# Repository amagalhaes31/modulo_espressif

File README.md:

# Modulo Conectividade com Espressif
Módulo Espressif com conectividades Wi-Fi, ETH, LTE, GPS e BLE.

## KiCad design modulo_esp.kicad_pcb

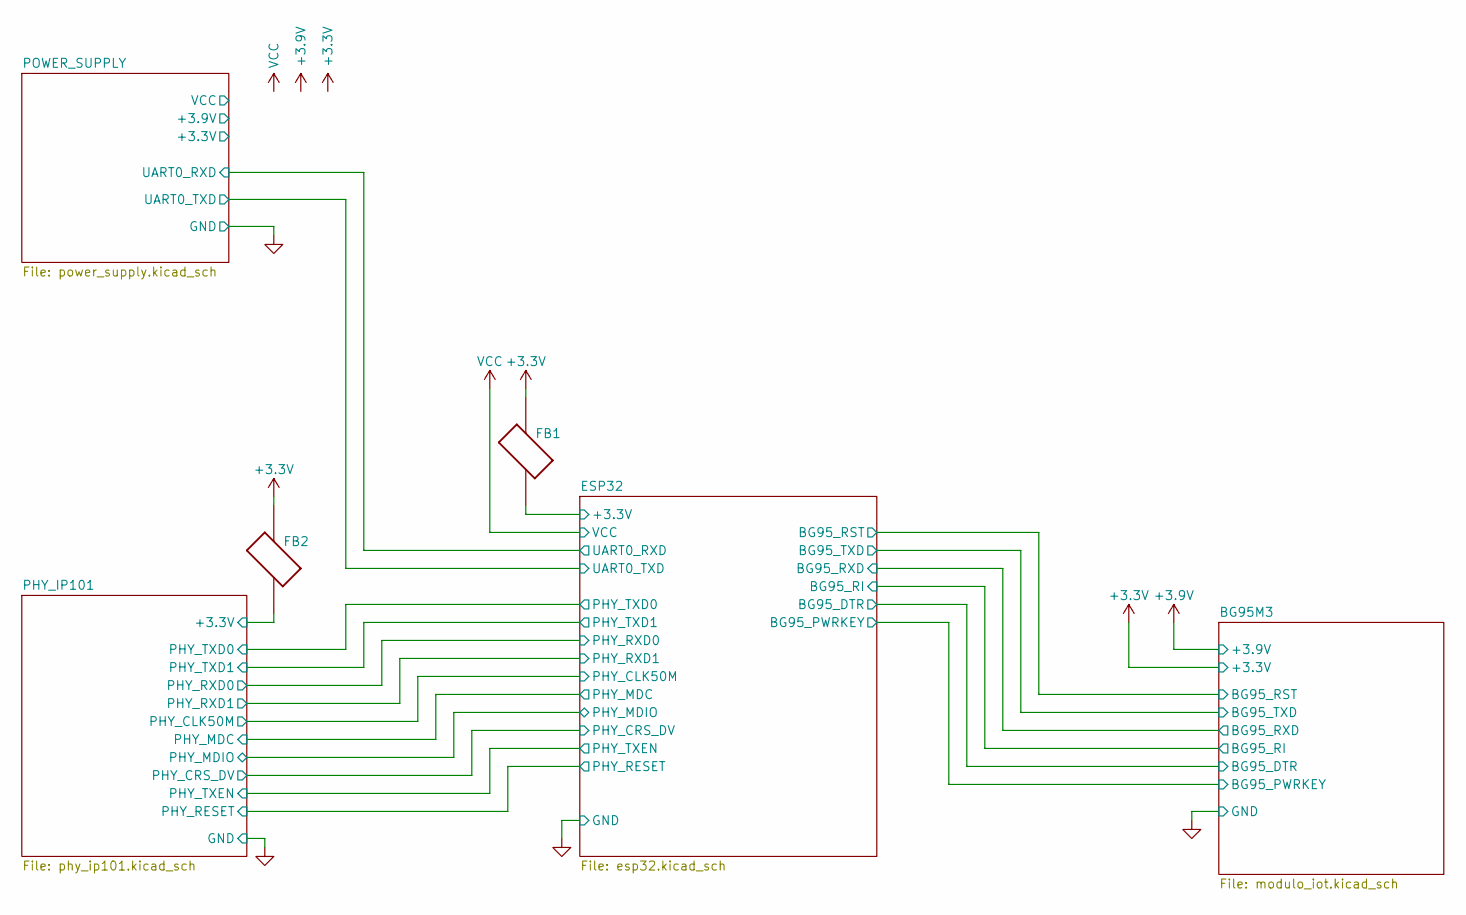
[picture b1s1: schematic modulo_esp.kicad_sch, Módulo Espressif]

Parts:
FB1, FB2: MPZ2012S102AT000; BEADC2012X105N; PARTREV 20190423

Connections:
+3V3: FB1.1, FB1.2, FB2.1, FB2.2; also elsewhere on the board

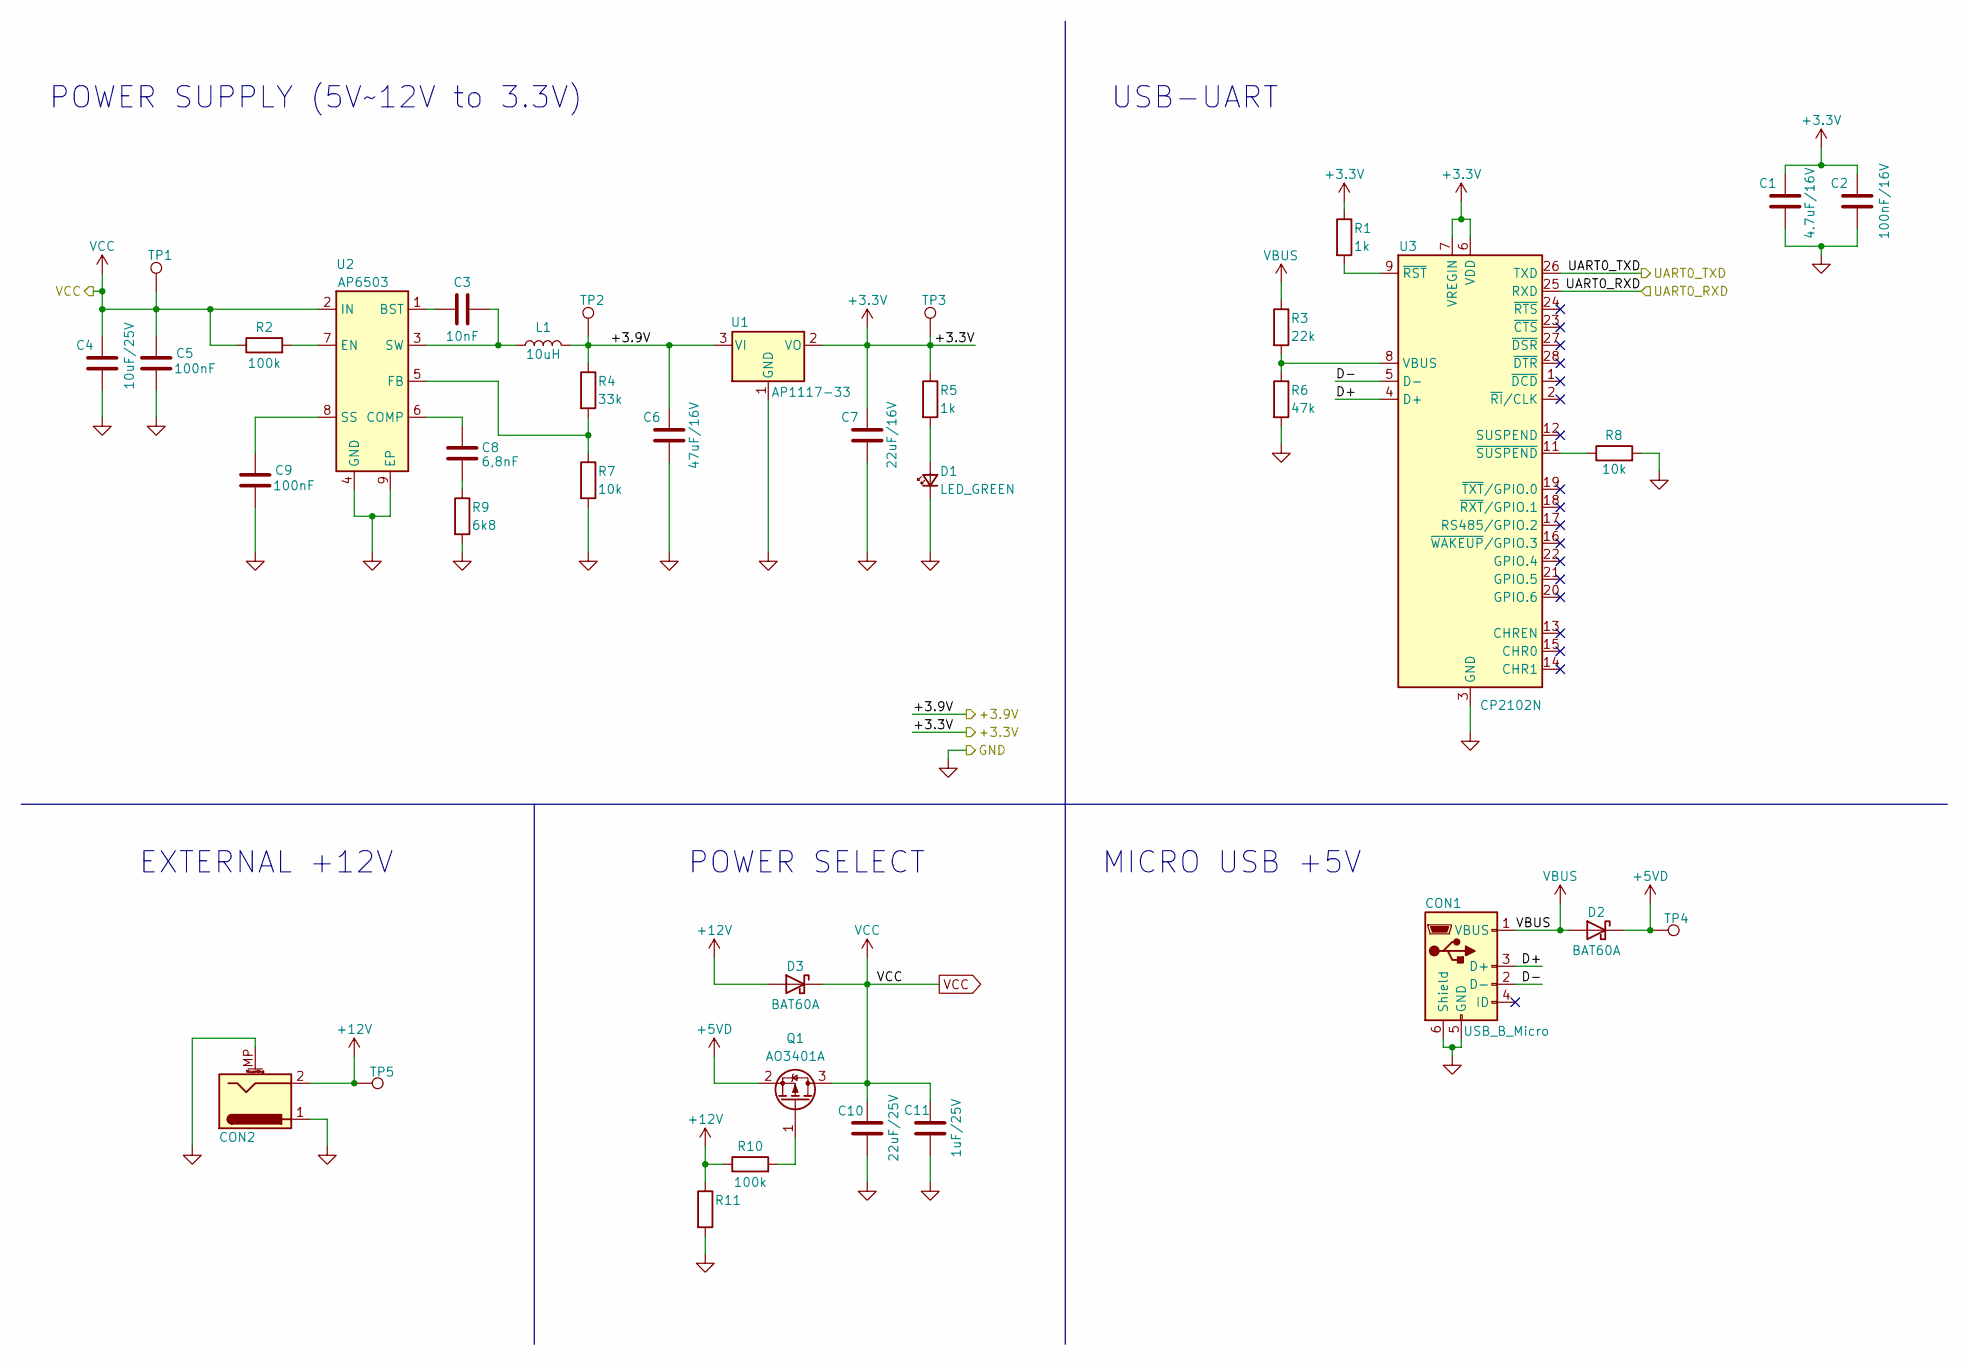
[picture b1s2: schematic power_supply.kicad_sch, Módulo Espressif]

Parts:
C1: 4.7uF/16V; C_1206_3216Metric_Pad1.33x1.80mm_HandSolder
C2: 100nF/16V; C_0603_1608Metric_Pad1.08x0.95mm_HandSolder
C3: 10nF; C_0603_1608Metric_Pad1.08x0.95mm_HandSolder
C4: 10uF/25V; C_1206_3216Metric_Pad1.33x1.80mm_HandSolder
C5, C9: 100nF; C_0603_1608Metric_Pad1.08x0.95mm_HandSolder
C6: 47uF/16V; C_1206_3216Metric_Pad1.33x1.80mm_HandSolder
C7: 22uF/16V; C_1206_3216Metric_Pad1.33x1.80mm_HandSolder
C8: 6,8nF; C_0603_1608Metric_Pad1.08x0.95mm_HandSolder
C10: 22uF/25V; C_1206_3216Metric_Pad1.33x1.80mm_HandSolder
C11: 1uF/25V; C_0603_1608Metric_Pad1.08x0.95mm_HandSolder
CON1: USB_B_Micro; USB_Micro-B_GCT_USB3076-30-A
CON2: Barrel_Jack_MountingPin; BarrelJack_GCT_DCJ200-10-A_Horizontal
D1: LED_GREEN; LED_0603_1608Metric_Pad1.05x0.95mm_HandSolder
D2, D3: BAT60A; D_SOD-323
L1: 10uH; L_Bourns-SRN8040_8x8.15mm
Q1: AO3401A; SOT-23
R1, R5: 1k; R_0603_1608Metric_Pad0.98x0.95mm_HandSolder
R2, R10: 100k; R_0603_1608Metric_Pad0.98x0.95mm_HandSolder
R3: 22k; R_0603_1608Metric_Pad0.98x0.95mm_HandSolder
R4: 33k; R_0603_1608Metric_Pad0.98x0.95mm_HandSolder
R6: 47k; R_0603_1608Metric_Pad0.98x0.95mm_HandSolder
R7, R8: 10k; R_0603_1608Metric_Pad0.98x0.95mm_HandSolder
R9: 6k8; R_0603_1608Metric_Pad0.98x0.95mm_HandSolder
R11: (no value)
TP1, TP2, TP3, TP4, TP5: TestPoint; TestPoint_Pad_1.5x1.5mm
U1: AP1117-33; SOT-223-3_TabPin2
U2: AP6503; SOIC-8-1EP_3.9x4.9mm_P1.27mm_EP2.41x3.81mm_ThermalVias
U3: CP2102N; QFN-28-1EP_5x5mm_P0.5mm_EP3.35x3.35mm

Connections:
+3V3: C1.1, C2.2, C7.1, R1.1, R5.1, TP3.1, U1.2 (VO), U3.6 (VDD), U3.7 (VREGIN); also elsewhere on the board
+5VD: D2.1 (K), Q1.2 (S), TP4.1
+12V: CON2.2, D3.2 (A), R10.1, R11.1, TP5.1
/ESP32/UART0_RXD: U3.25 (RXD); also elsewhere on the board
/ESP32/UART0_TXD: U3.26 (TXD); also elsewhere on the board
/POWER_SUPPLY/+3.9V: C6.1, L1.2, R4.1, TP2.1, U1.3 (VI)
/POWER_SUPPLY/D+: CON1.3 (D+), U3.4 (D+)
/POWER_SUPPLY/D-: CON1.2 (D-), U3.5 (D-)
unnamed: C3.1, U2.1 (BST)
unnamed: C3.2, L1.1, U2.3 (SW)
unnamed: C8.1, U2.6 (COMP)
unnamed: C8.2, R9.1
unnamed: C9.2, U2.8 (SS)
unnamed: D1.2 (A), R5.2
unnamed: Q1.1 (G), R10.2
unnamed: R1.2, U3.9 (~RST)
unnamed: R2.2, U2.7 (EN)
unnamed: R3.2, R6.1, U3.8 (VBUS)
unnamed: R4.2, R7.1, U2.5 (FB)
unnamed: R8.1, U3.11 (~SUSPEND)
VBUS: CON1.1 (VBUS), D2.2 (A), R3.1
VCC: C4.1, C5.2, C10.1, C11.1, D3.1 (K), Q1.3 (D), R2.1, TP1.1, U2.2 (IN)

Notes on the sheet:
EXTERNAL +12V
POWER SELECT
MICRO USB +5V
POWER SUPPLY (5V~12V to 3.3V)
USB-UART

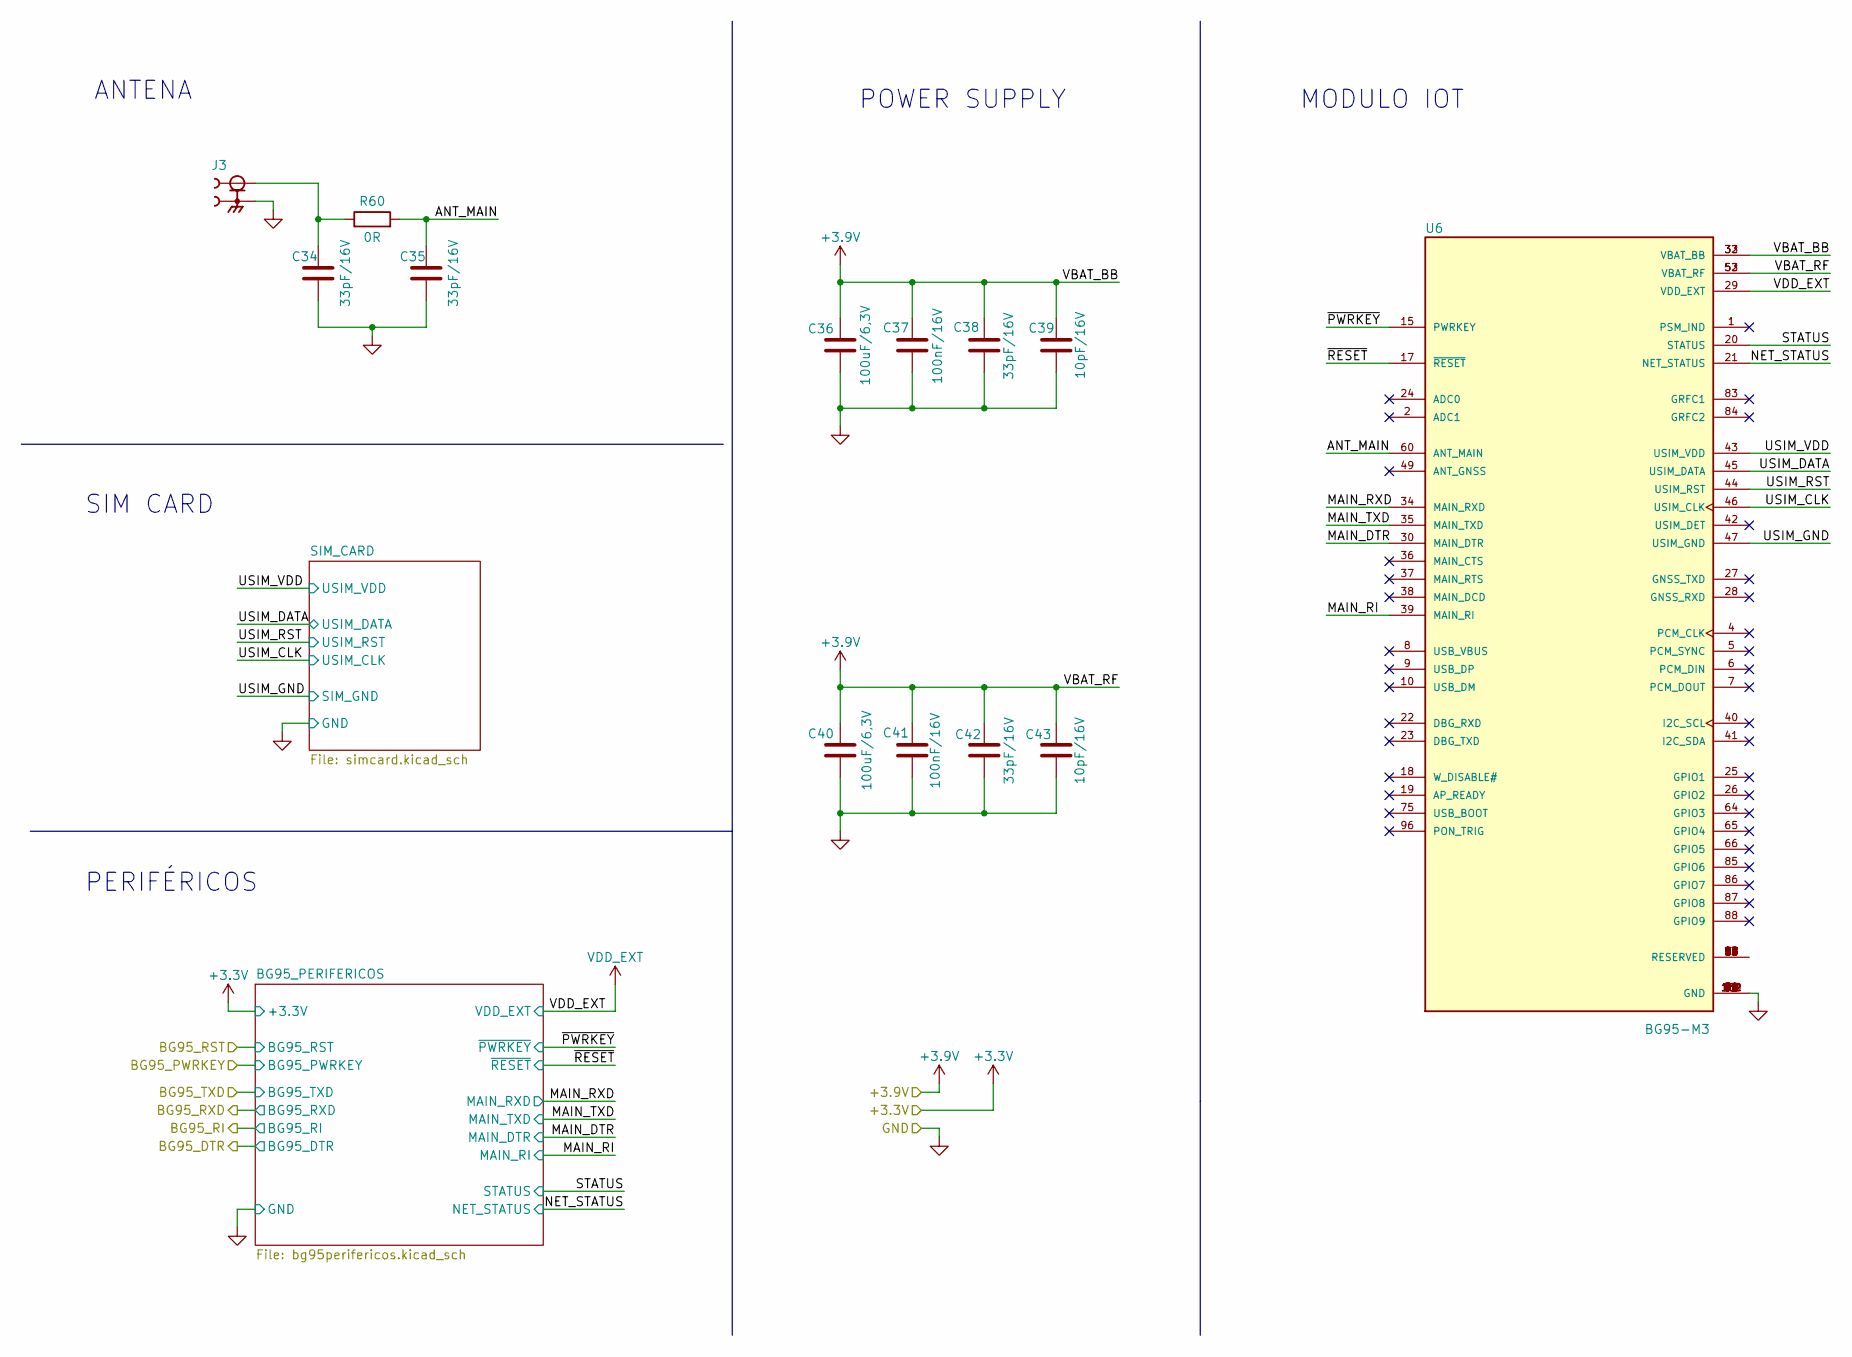
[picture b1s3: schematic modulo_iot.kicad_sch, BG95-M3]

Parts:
C34, C35: 33pF/16V; C_0402_1005Metric_Pad0.74x0.62mm_HandSolder
C36, C40: 100uF/6,3V; C_1206_3216Metric_Pad1.33x1.80mm_HandSolder
C37, C41: 100nF/16V; C_0603_1608Metric_Pad1.08x0.95mm_HandSolder
C38, C42: 33pF/16V; C_0603_1608Metric_Pad1.08x0.95mm_HandSolder
C39, C43: 10pF/16V; C_0603_1608Metric_Pad1.08x0.95mm_HandSolder
J3: SMA_CONNECTOR; LPRS_SMA_CONNECTOR; PARTREV 1.3
R60: 0R; R_0603_1608Metric_Pad0.98x0.95mm_HandSolder
U6: BG95-M3; XCVR_BG95; PARTREV 1.1

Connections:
+3V3: C36.1, C37.2, C38.2, C39.2, C40.1, C41.2, C42.2, C43.2, U6.29 (VDD_EXT), U6.32 (VBAT_BB), U6.33 (VBAT_BB), U6.52 (VBAT_RF), U6.53 (VBAT_RF); also elsewhere on the board
/BG95M3/ANT_MAIN: C35.2, R60.2, U6.60 (ANT_MAIN)
/BG95M3/MAIN_DTR: U6.30 (MAIN_DTR); also elsewhere on the board
/BG95M3/MAIN_RI: U6.39 (MAIN_RI); also elsewhere on the board
/BG95M3/MAIN_RXD: U6.34 (MAIN_RXD); also elsewhere on the board
/BG95M3/MAIN_TXD: U6.35 (MAIN_TXD); also elsewhere on the board
/BG95M3/NET_STATUS: U6.21 (NET_STATUS); also elsewhere on the board
/BG95M3/STATUS: U6.20 (STATUS); also elsewhere on the board
/BG95M3/USIM_CLK: U6.46 (USIM_CLK); also elsewhere on the board
/BG95M3/USIM_DATA: U6.45 (USIM_DATA); also elsewhere on the board
/BG95M3/USIM_GND: U6.47 (USIM_GND); also elsewhere on the board
/BG95M3/USIM_RST: U6.44 (USIM_RST); also elsewhere on the board
/BG95M3/USIM_VDD: U6.43 (USIM_VDD); also elsewhere on the board
/BG95M3/~PWRKEY: U6.15 (PWRKEY); also elsewhere on the board
/BG95M3/~RESET: U6.17 (~RESET); also elsewhere on the board
unnamed: C34.2, J3.1, R60.1
unnamed: U6.11 (RESERVED), U6.12 (RESERVED), U6.13 (RESERVED), U6.14 (RESERVED), U6.16 (RESERVED), U6.51 (RESERVED), U6.56 (RESERVED), U6.57 (RESERVED), U6.63 (RESERVED), U6.76 (RESERVED), U6.77 (RESERVED), U6.78 (RESERVED), U6.92 (RESERVED), U6.93 (RESERVED), U6.94 (RESERVED), U6.95 (RESERVED), U6.97 (RESERVED), U6.98 (RESERVED), U6.99 (RESERVED)

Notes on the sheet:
MODULO IOT
PERIFÉRICOS
ANTENA
POWER SUPPLY
SIM CARD

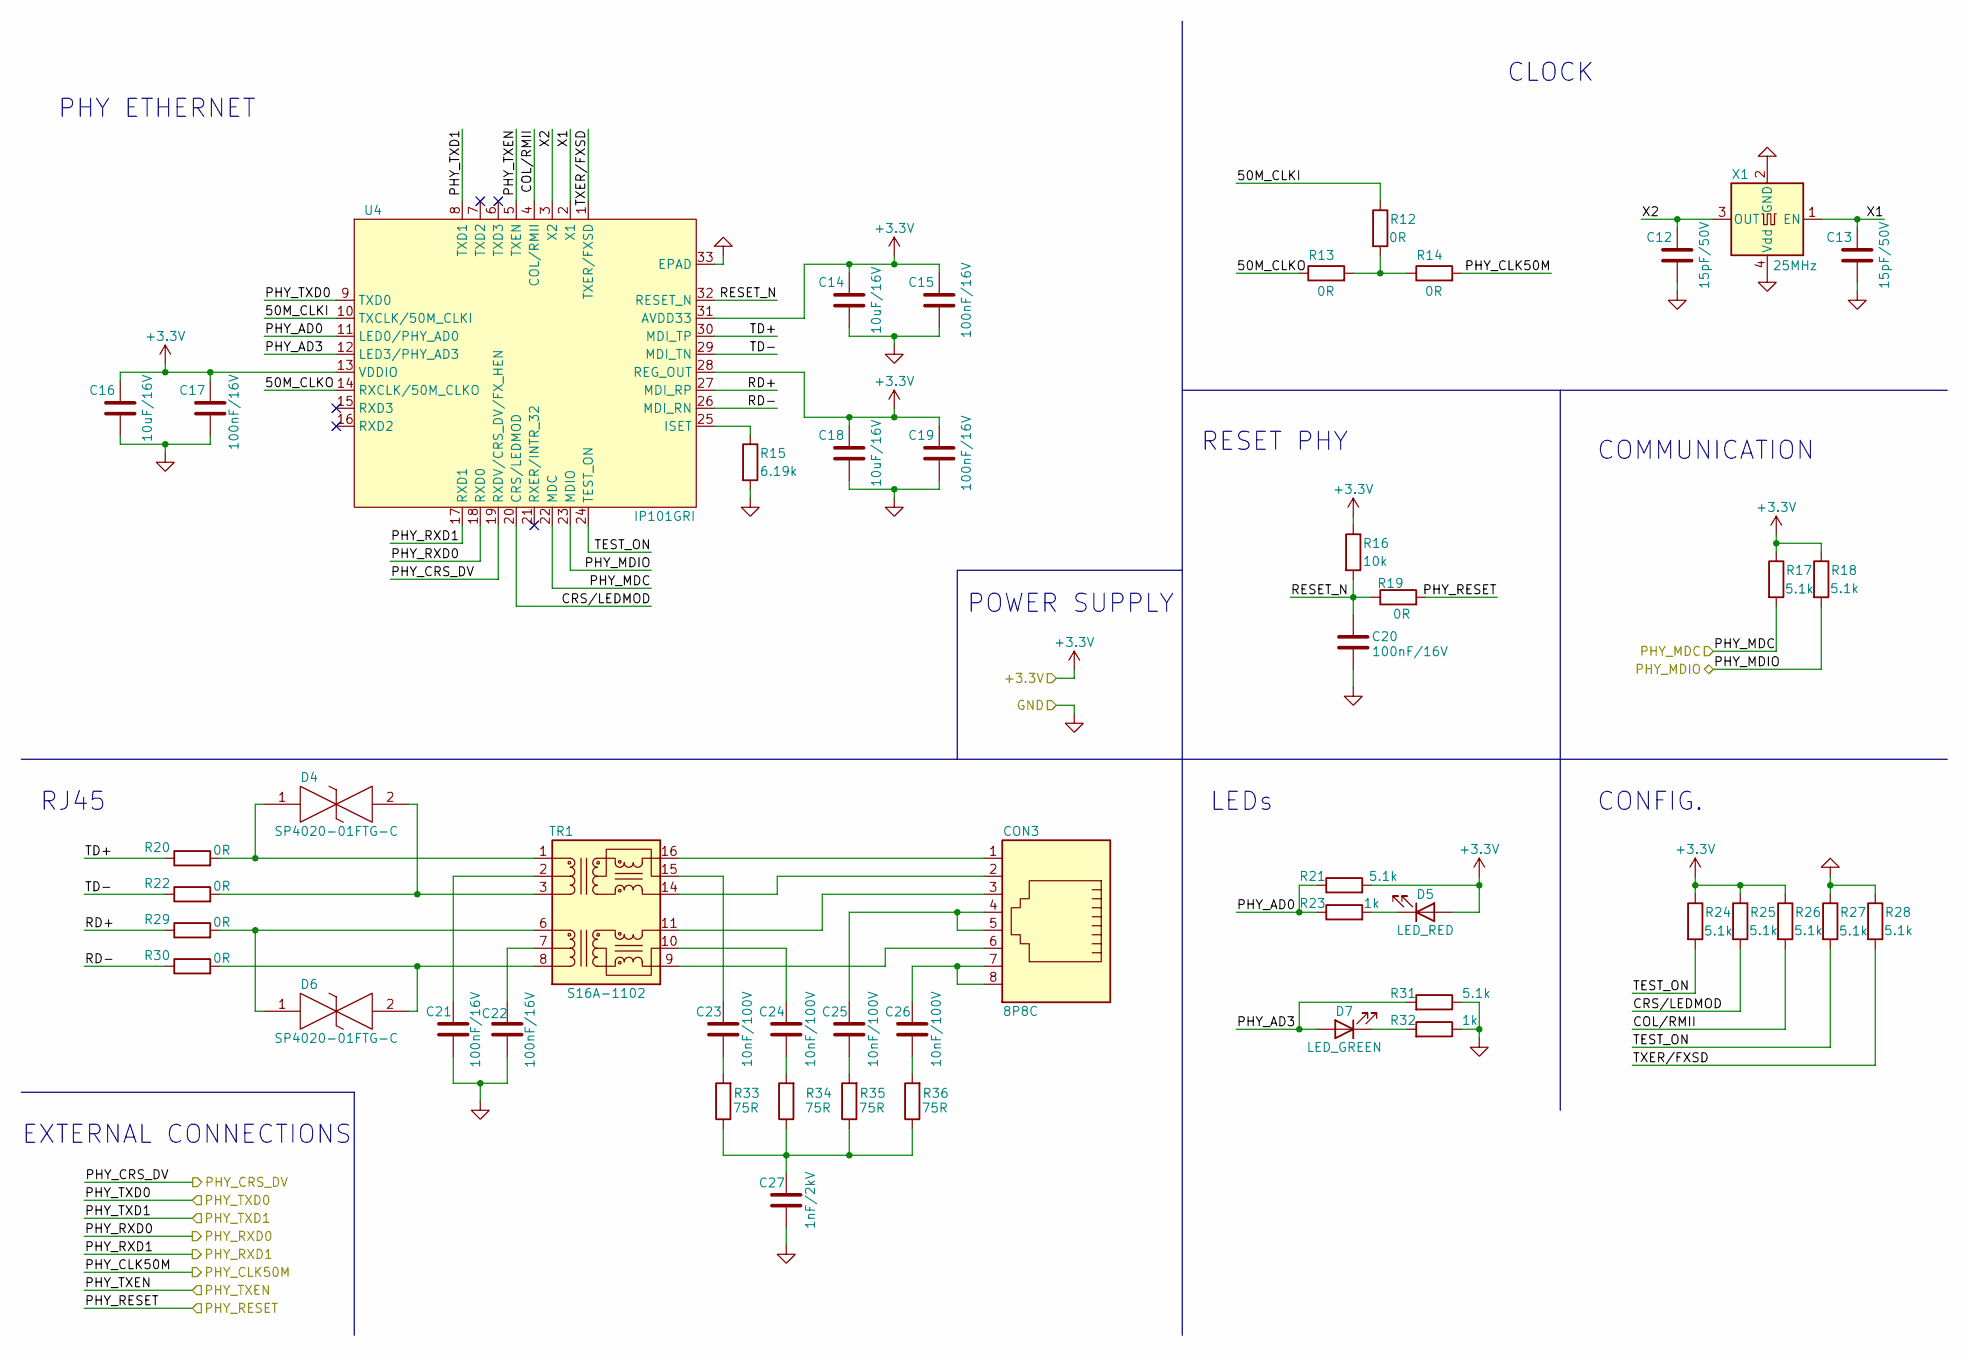
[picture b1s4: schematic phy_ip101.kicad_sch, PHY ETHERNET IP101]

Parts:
C12, C13: 15pF/50V; C_0603_1608Metric_Pad1.08x0.95mm_HandSolder
C14, C16, C18: 10uF/16V; C_0603_1608Metric_Pad1.08x0.95mm_HandSolder
C15, C17, C19, C20, C21, C22: 100nF/16V; C_0603_1608Metric_Pad1.08x0.95mm_HandSolder
C23, C24, C25, C26: 10nF/100V; C_0603_1608Metric_Pad1.08x0.95mm_HandSolder
C27: 1nF/2kV; C_1210_3225Metric_Pad1.33x2.70mm_HandSolder
CON3: 8P8C; RJ45_OST_PJ012-8P8CX_Vertical
D4, D6: SP4020-01FTG-C; D_SOD-323_HandSoldering; Manufacturer_Part_Number SP4020-01FTG-C; Mouser Part Number 576-SP4020-01FTG-C
D5: LED_RED; LED_0603_1608Metric_Pad1.05x0.95mm_HandSolder
D7: LED_GREEN; LED_0603_1608Metric_Pad1.05x0.95mm_HandSolder
R12, R13, R14, R19, R20, R22, R29, R30: 0R; R_0603_1608Metric_Pad0.98x0.95mm_HandSolder
R15: 6.19k; R_0603_1608Metric_Pad0.98x0.95mm_HandSolder
R16: 10k; R_0603_1608Metric_Pad0.98x0.95mm_HandSolder
R17, R18, R21, R24, R25, R26, R27, R28, R31: 5.1k; R_0603_1608Metric_Pad0.98x0.95mm_HandSolder
R23, R32: 1k; R_0603_1608Metric_Pad0.98x0.95mm_HandSolder
R33, R34, R35, R36: 75R; R_0603_1608Metric_Pad0.98x0.95mm_HandSolder
TR1: S16A-1102; Transformer_Ethernet_Wuerth_749013011A
U4: IP101GRI; QFN-32-1EP_4x4mm_P0.4mm_EP2.65x2.65mm_ThermalVias
X1: 25MHz; Oscillator_SMD_Abracon_ASE-4Pin_3.2x2.5mm

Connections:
+3V3: C14.2, C15.2, C16.2, C17.2, C18.2, C19.2, D5.2 (A), R16.1, R17.1, R18.1, R21.2, R24.1, R25.1, R26.1, U4.13 (VDDIO), U4.28 (REG_OUT), U4.31 (AVDD33); also elsewhere on the board
/ESP32/PHY_CLK50M: R14.2; also elsewhere on the board
/ESP32/PHY_CRS_DV: U4.19 (RXDV/CRS_DV/FX_HEN); also elsewhere on the board
/ESP32/PHY_MDC: R17.2, U4.22 (MDC); also elsewhere on the board
/ESP32/PHY_MDIO: R18.2, U4.23 (MDIO); also elsewhere on the board
/ESP32/PHY_RXD0: U4.18 (RXD0); also elsewhere on the board
/ESP32/PHY_RXD1: U4.17 (RXD1); also elsewhere on the board
/ESP32/PHY_TXD0: U4.9 (TXD0); also elsewhere on the board
/ESP32/PHY_TXD1: R19.2, U4.8 (TXD1); also elsewhere on the board
/ESP32/PHY_TXEN: U4.5 (TXEN); also elsewhere on the board
/PHY_IP101/50M_CLKI: R12.1, U4.10 (TXCLK/50M_CLKI)
/PHY_IP101/50M_CLKO: R13.1, U4.14 (RXCLK/50M_CLKO)
/PHY_IP101/COL/RMII: R26.2, U4.4 (COL/RMII)
/PHY_IP101/CRS/LEDMOD: R25.2, U4.20 (CRS/LEDMOD)
/PHY_IP101/PHY_AD0: R21.1, R23.1, U4.11 (LED0/PHY_AD0)
/PHY_IP101/PHY_AD3: D7.2 (A), R31.2, U4.12 (LED3/PHY_AD3)
/PHY_IP101/RD+: R29.1, U4.27 (MDI_RP)
/PHY_IP101/RD-: R30.1, U4.26 (MDI_RN)
/PHY_IP101/RESET_N: C20.2, R16.2, R19.1, U4.32 (RESET_N)
/PHY_IP101/TD+: R20.1, U4.30 (MDI_TP)
/PHY_IP101/TD-: R22.1, U4.29 (MDI_TN)
/PHY_IP101/TEST_ON: R24.2, R27.2, U4.24 (TEST_ON)
/PHY_IP101/TXER/FXSD: R28.2, U4.1 (TXER/FXSD)
/PHY_IP101/X1: C13.2, U4.2 (X1), X1.1 (EN)
/PHY_IP101/X2: C12.2, U4.3 (X2), X1.3 (OUT)
unnamed: C21.2, TR1.2 (C_TD)
unnamed: C22.2, TR1.7 (C_RD)
unnamed: C23.1, R33.2
unnamed: C23.2, TR1.15 (C_TX)
unnamed: C24.1, R34.2
unnamed: C24.2, TR1.10 (C_RX)
unnamed: C25.1, R35.2
unnamed: C25.2, CON3.4, CON3.5
unnamed: C26.1, R36.2
unnamed: C26.2, CON3.7, CON3.8
unnamed: C27.2, R33.1, R34.1, R35.1, R36.1
unnamed: CON3.1, TR1.16 (TX+)
unnamed: CON3.2, TR1.14 (TX-)
unnamed: CON3.3, TR1.11 (RX+)
unnamed: CON3.6, TR1.9 (RX-)
unnamed: D4.1, R20.2, TR1.1 (TD+)
unnamed: D4.2, R22.2, TR1.3 (TD-)
unnamed: D5.1 (K), R23.2
unnamed: D6.1, R29.2, TR1.6 (RD+)
unnamed: D6.2, R30.2, TR1.8 (RD-)
unnamed: D7.1 (K), R32.2
unnamed: R12.2, R13.2, R14.1
unnamed: R15.1, U4.25 (ISET)

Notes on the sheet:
POWER SUPPLY
CLOCK
EXTERNAL CONNECTIONS
LEDs
CONFIG.
RESET PHY
RJ45
PHY ETHERNET
COMMUNICATION

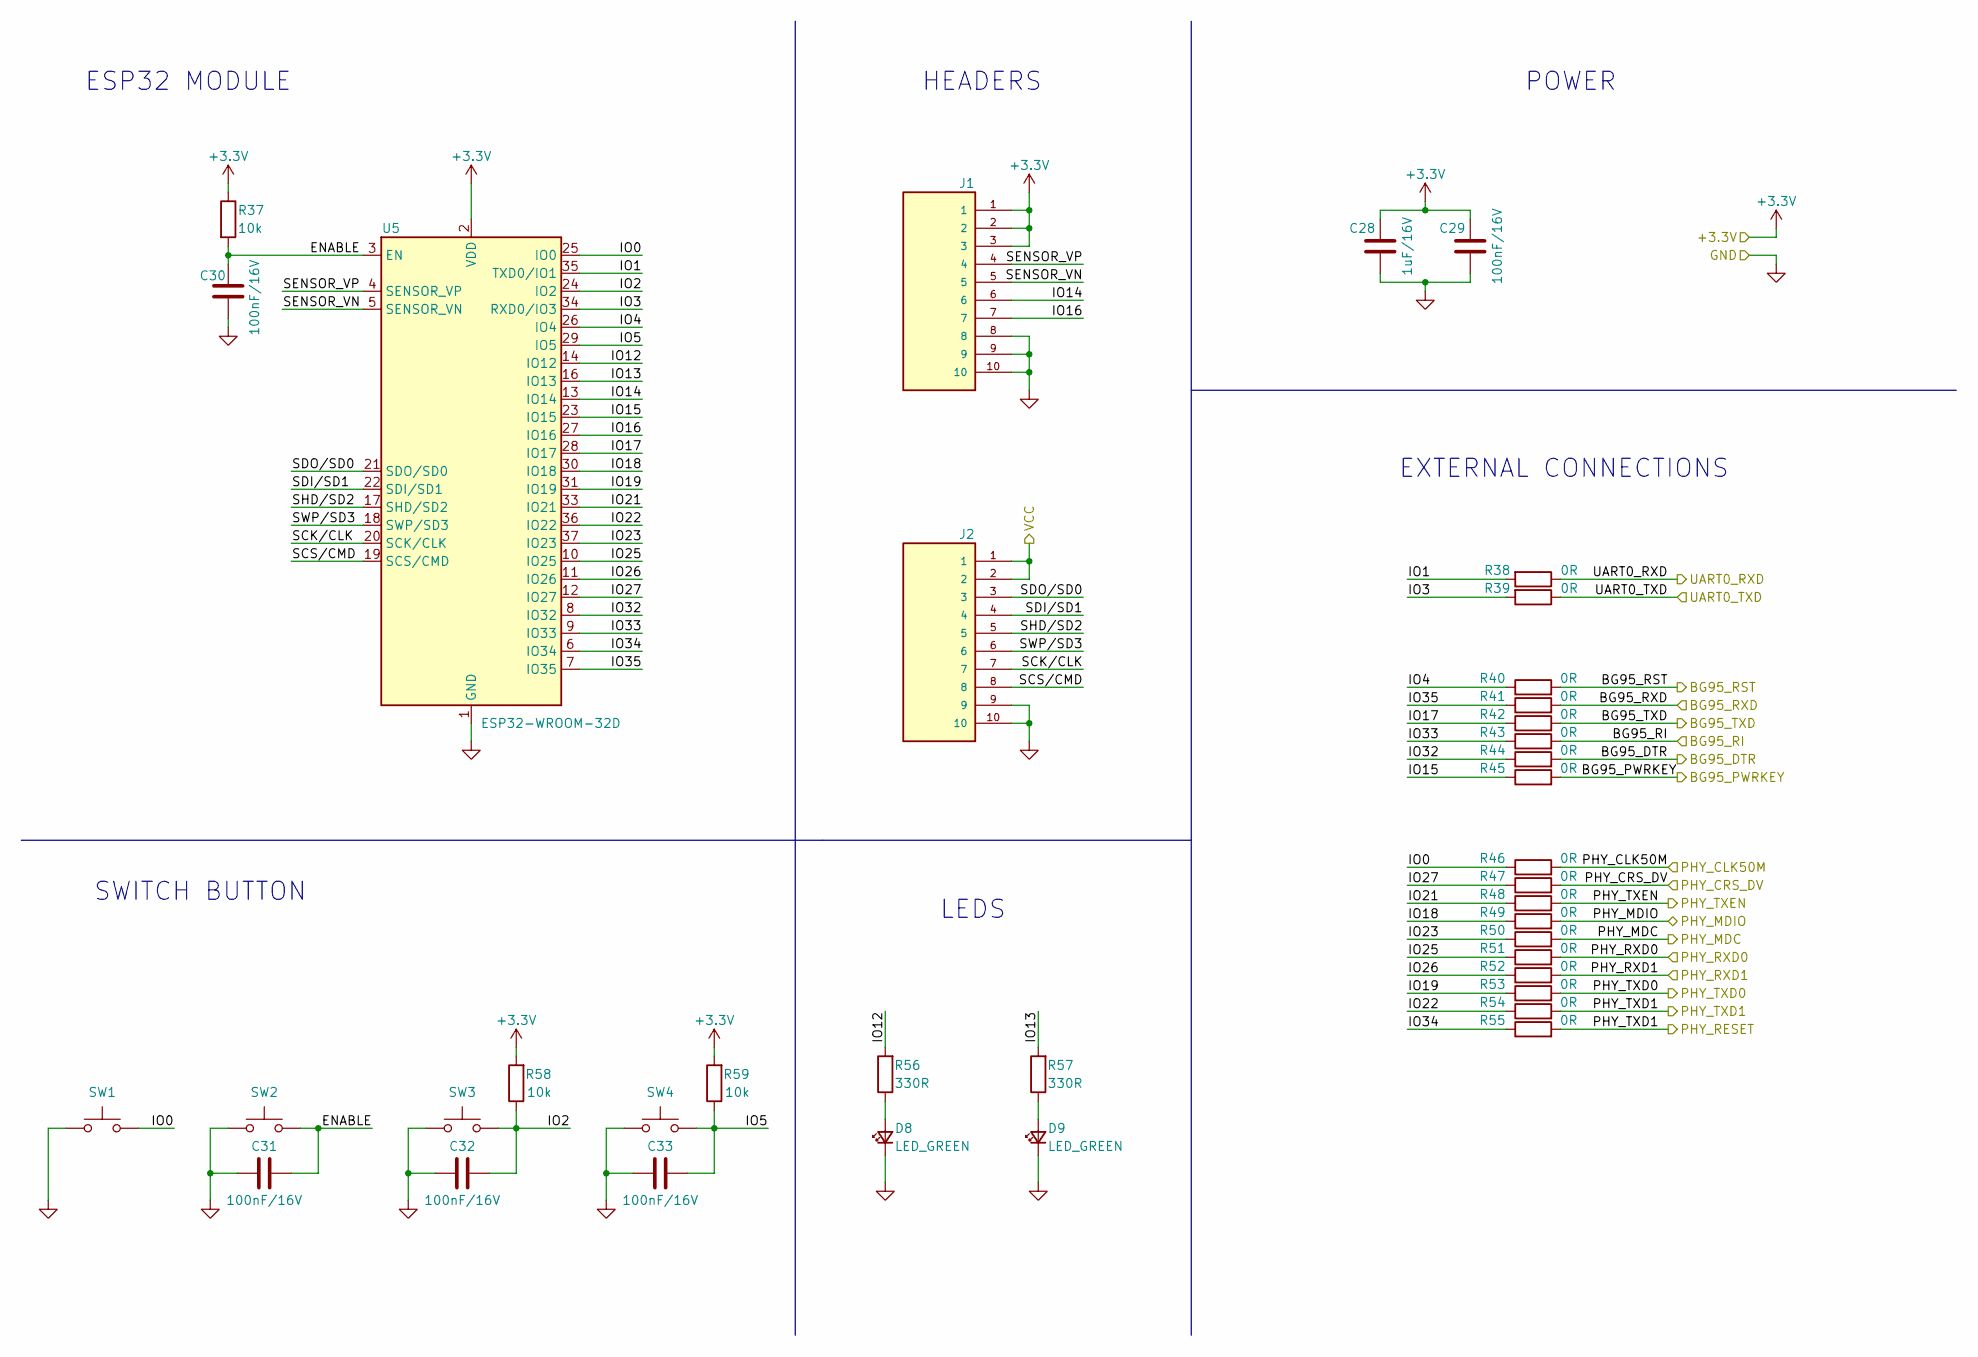
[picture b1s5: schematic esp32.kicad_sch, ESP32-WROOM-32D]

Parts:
C28: 1uF/16V; C_0603_1608Metric_Pad1.08x0.95mm_HandSolder
C29, C30, C31, C32, C33: 100nF/16V; C_0603_1608Metric_Pad1.08x0.95mm_HandSolder
D8, D9: LED_GREEN; LED_0603_1608Metric_Pad1.05x0.95mm_HandSolder
J1, J2: 104426-8; TE_104426-8
R37, R58, R59: 10k; R_0603_1608Metric_Pad0.98x0.95mm_HandSolder
R38, R39, R40, R41, R42, R43, R44, R45, R46, R47, R48, R49, R50, R51, R52, R53, R54, R55: 0R; R_0603_1608Metric_Pad0.98x0.95mm_HandSolder
R56, R57: 330R; R_0603_1608Metric_Pad0.98x0.95mm_HandSolder
SW1, SW2, SW3, SW4: SW_Push; SW_SPST_CK_RS282G05A3
U5: ESP32-WROOM-32D; ESP32-WROOM-32

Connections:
+3V3: C28.2, C29.2, J1.1, J1.2, J1.3, J2.1, J2.2, R37.1, R58.2, R59.2, U5.2 (VDD); also elsewhere on the board
/ESP32/BG95_DTR: R44.2; also elsewhere on the board
/ESP32/BG95_PWRKEY: R45.2; also elsewhere on the board
/ESP32/BG95_RI: R43.2; also elsewhere on the board
/ESP32/BG95_RST: R40.2; also elsewhere on the board
/ESP32/BG95_RXD: R41.2; also elsewhere on the board
/ESP32/BG95_TXD: R42.2; also elsewhere on the board
/ESP32/ENABLE: C30.2, C31.1, R37.2, SW2.2, U5.3 (EN)
/ESP32/IO0: R46.1, SW1.2, U5.25 (IO0)
/ESP32/IO1: R38.2, U5.35 (TXD0/IO1)
/ESP32/IO2: C32.1, R58.1, SW3.2, U5.24 (IO2)
/ESP32/IO3: R39.2, U5.34 (RXD0/IO3)
/ESP32/IO4: R40.1, U5.26 (IO4)
/ESP32/IO5: C33.1, R59.1, SW4.2, U5.29 (IO5)
/ESP32/IO12: R56.2, U5.14 (IO12)
/ESP32/IO13: R57.2, U5.16 (IO13)
/ESP32/IO14: J1.6, U5.13 (IO14)
/ESP32/IO15: R45.1, U5.23 (IO15)
/ESP32/IO16: J1.7, U5.27 (IO16)
/ESP32/IO17: R42.1, U5.28 (IO17)
/ESP32/IO18: R49.1, U5.30 (IO18)
/ESP32/IO19: R53.1, U5.31 (IO19)
/ESP32/IO21: R48.1, U5.33 (IO21)
/ESP32/IO22: R54.1, U5.36 (IO22)
/ESP32/IO23: R50.1, U5.37 (IO23)
/ESP32/IO25: R51.1, U5.10 (IO25)
/ESP32/IO26: R52.1, U5.11 (IO26)
/ESP32/IO27: R47.1, U5.12 (IO27)
/ESP32/IO32: R44.1, U5.8 (IO32)
/ESP32/IO33: R43.1, U5.9 (IO33)
/ESP32/IO34: R55.1, U5.6 (IO34)
/ESP32/IO35: R41.1, U5.7 (IO35)
/ESP32/PHY_CLK50M: R46.2; also elsewhere on the board
/ESP32/PHY_CRS_DV: R47.2; also elsewhere on the board
/ESP32/PHY_MDC: R50.2; also elsewhere on the board
/ESP32/PHY_MDIO: R49.2; also elsewhere on the board
/ESP32/PHY_RXD0: R51.2; also elsewhere on the board
/ESP32/PHY_RXD1: R52.2; also elsewhere on the board
/ESP32/PHY_TXD0: R53.2; also elsewhere on the board
/ESP32/PHY_TXD1: R54.2, R55.2; also elsewhere on the board
/ESP32/PHY_TXEN: R48.2; also elsewhere on the board
/ESP32/SCK/CLK: J2.7, U5.20 (SCK/CLK)
/ESP32/SCS/CMD: J2.8, U5.19 (SCS/CMD)
/ESP32/SDI/SD1: J2.4, U5.22 (SDI/SD1)
/ESP32/SDO/SD0: J2.3, U5.21 (SDO/SD0)
/ESP32/SENSOR_VN: J1.5, U5.5 (SENSOR_VN)
/ESP32/SENSOR_VP: J1.4, U5.4 (SENSOR_VP)
/ESP32/SHD/SD2: J2.5, U5.17 (SHD/SD2)
/ESP32/SWP/SD3: J2.6, U5.18 (SWP/SD3)
/ESP32/UART0_RXD: R38.1; also elsewhere on the board
/ESP32/UART0_TXD: R39.1; also elsewhere on the board
unnamed: D8.2 (A), R56.1
unnamed: D9.2 (A), R57.1

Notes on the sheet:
LEDS
POWER
ESP32 MODULE
HEADERS
EXTERNAL CONNECTIONS
SWITCH BUTTON

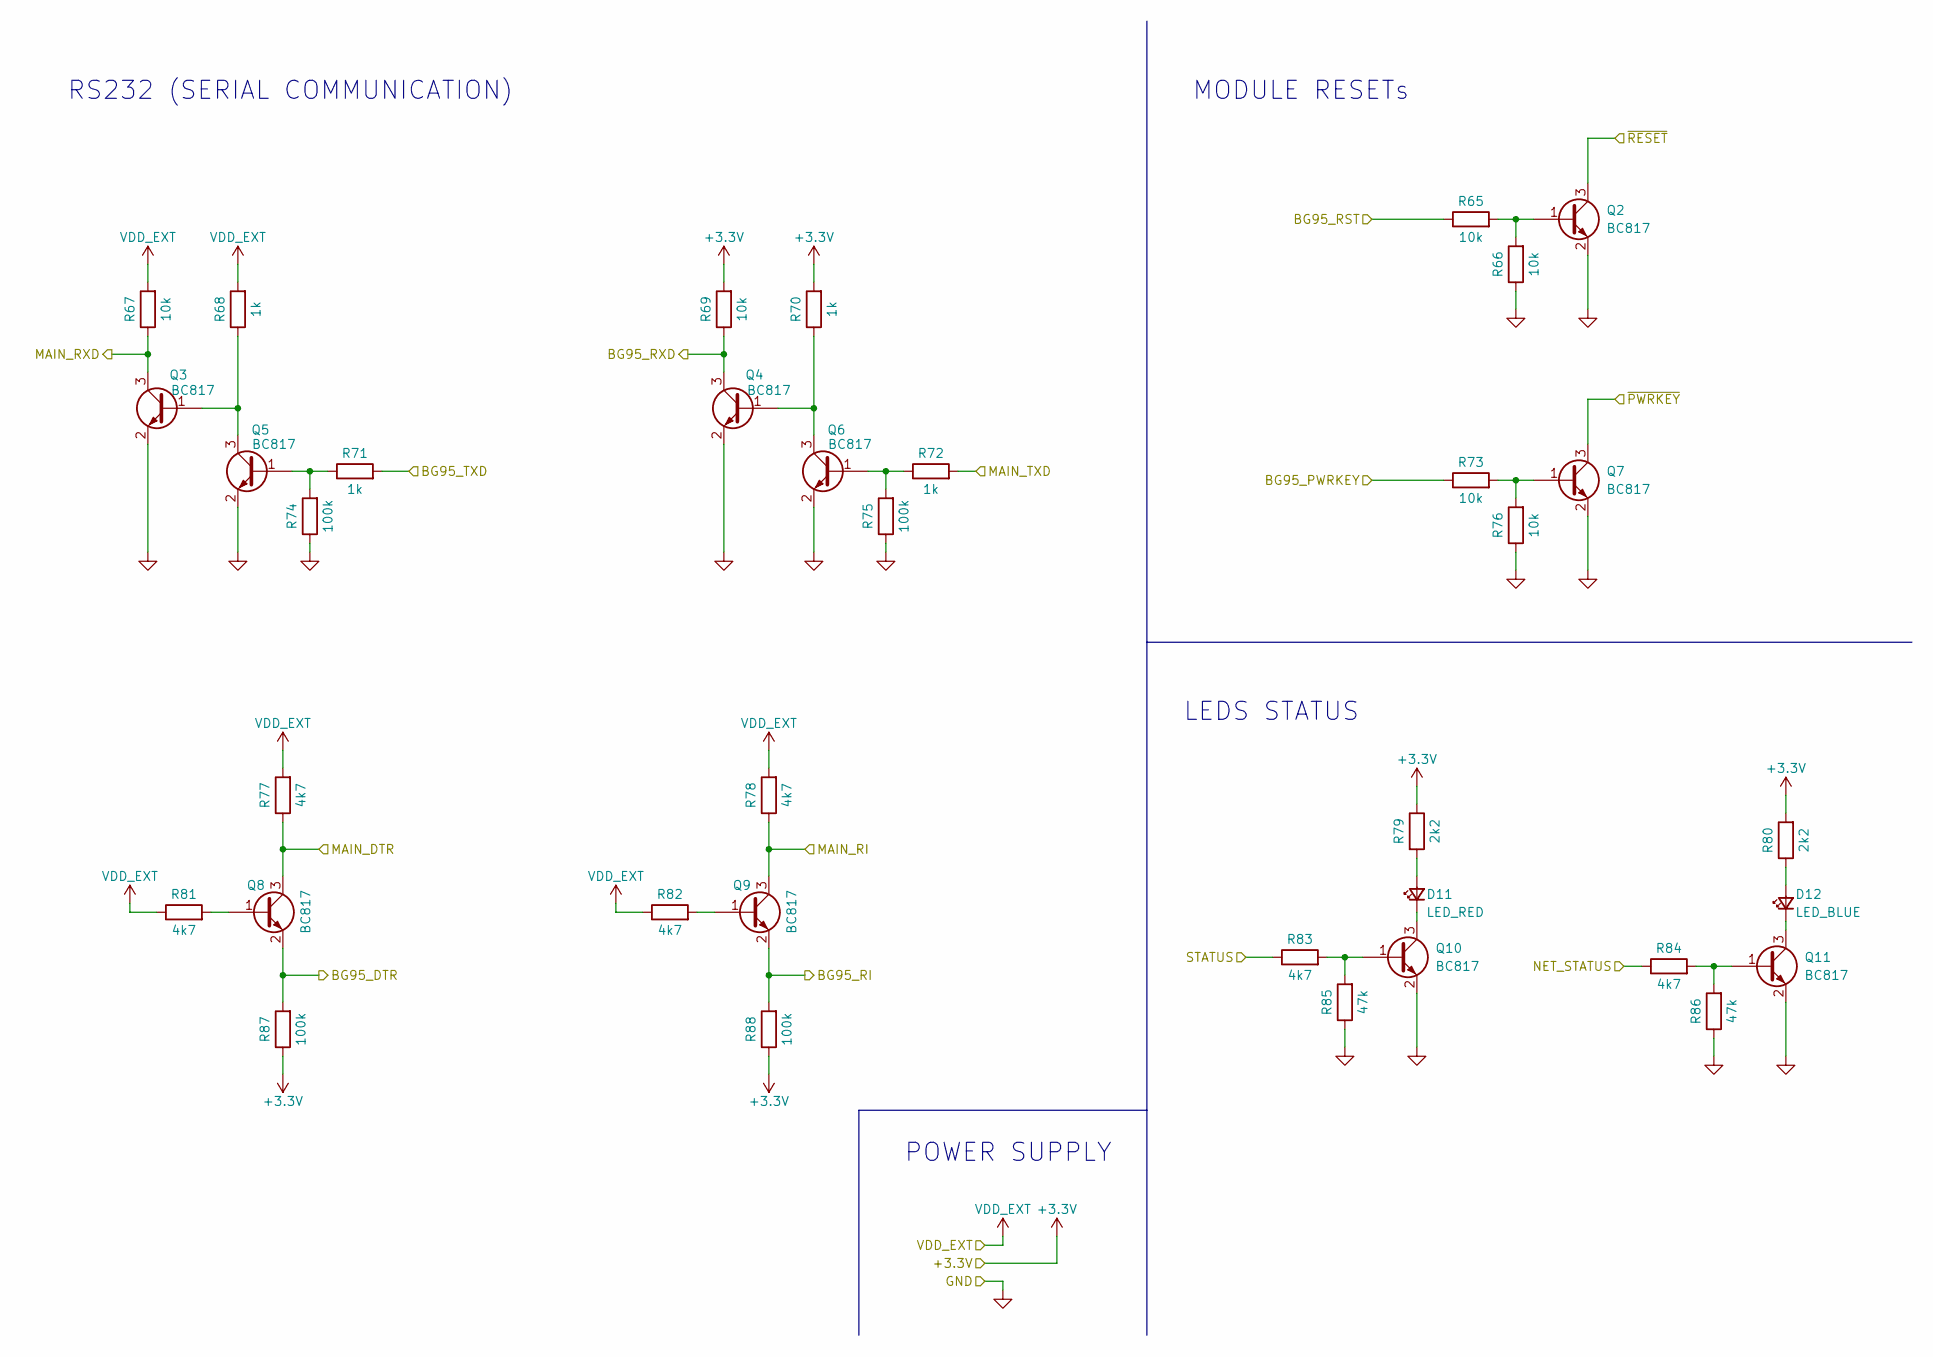
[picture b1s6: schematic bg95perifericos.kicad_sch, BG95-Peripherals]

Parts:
D11: LED_RED; LED_0603_1608Metric_Pad1.05x0.95mm_HandSolder
D12: LED_BLUE; LED_0603_1608Metric_Pad1.05x0.95mm_HandSolder
Q2, Q3, Q4, Q5, Q6, Q7, Q8, Q9, Q10, Q11: BC817; SOT-23
R65, R66, R67, R69, R73, R76: 10k; R_0603_1608Metric_Pad0.98x0.95mm_HandSolder
R68, R70, R71, R72: 1k; R_0603_1608Metric_Pad0.98x0.95mm_HandSolder
R74, R75, R87, R88: 100k; R_0603_1608Metric_Pad0.98x0.95mm_HandSolder
R77, R78, R81, R82, R83, R84: 4k7; R_0603_1608Metric_Pad0.98x0.95mm_HandSolder
R79, R80: 2k2; R_0603_1608Metric_Pad0.98x0.95mm_HandSolder
R85, R86: 47k; R_0603_1608Metric_Pad0.98x0.95mm_HandSolder

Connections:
+3V3: R67.2, R68.2, R69.2, R70.2, R77.2, R78.2, R79.1, R80.2, R81.1, R82.1, R87.1, R88.1; also elsewhere on the board
/BG95M3/MAIN_DTR: Q8.3 (C), R77.1; also elsewhere on the board
/BG95M3/MAIN_RI: Q9.3 (C), R78.1; also elsewhere on the board
/BG95M3/MAIN_RXD: Q3.3 (C), R67.1; also elsewhere on the board
/BG95M3/MAIN_TXD: R72.2; also elsewhere on the board
/BG95M3/NET_STATUS: R84.1; also elsewhere on the board
/BG95M3/STATUS: R83.1; also elsewhere on the board
/BG95M3/~PWRKEY: Q7.3 (C); also elsewhere on the board
/BG95M3/~RESET: Q2.3 (C); also elsewhere on the board
/ESP32/BG95_DTR: Q8.2 (E), R87.2; also elsewhere on the board
/ESP32/BG95_PWRKEY: R73.1; also elsewhere on the board
/ESP32/BG95_RI: Q9.2 (E), R88.2; also elsewhere on the board
/ESP32/BG95_RST: R65.1; also elsewhere on the board
/ESP32/BG95_RXD: Q4.3 (C), R69.1; also elsewhere on the board
/ESP32/BG95_TXD: R71.2; also elsewhere on the board
unnamed: D11.1 (K), Q10.3 (C)
unnamed: D11.2 (A), R79.2
unnamed: D12.1 (K), Q11.3 (C)
unnamed: D12.2 (A), R80.1
unnamed: Q2.1 (B), R65.2, R66.2
unnamed: Q3.1 (B), Q5.3 (C), R68.1
unnamed: Q4.1 (B), Q6.3 (C), R70.1
unnamed: Q5.1 (B), R71.1, R74.2
unnamed: Q6.1 (B), R72.1, R75.2
unnamed: Q7.1 (B), R73.2, R76.2
unnamed: Q8.1 (B), R81.2
unnamed: Q9.1 (B), R82.2
unnamed: Q10.1 (B), R83.2, R85.2
unnamed: Q11.1 (B), R84.2, R86.2

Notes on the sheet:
LEDS STATUS
POWER SUPPLY
MODULE RESETs
RS232 (SERIAL COMMUNICATION)
